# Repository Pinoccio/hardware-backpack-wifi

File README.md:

wifi-hardware-reference
===========================

Contained are the schematics, board layout, data sheets, and BOM for the Pinoccio WiFi board.

The board revisions are also marked as tags in the git repository, if you'd like to see a previous version.

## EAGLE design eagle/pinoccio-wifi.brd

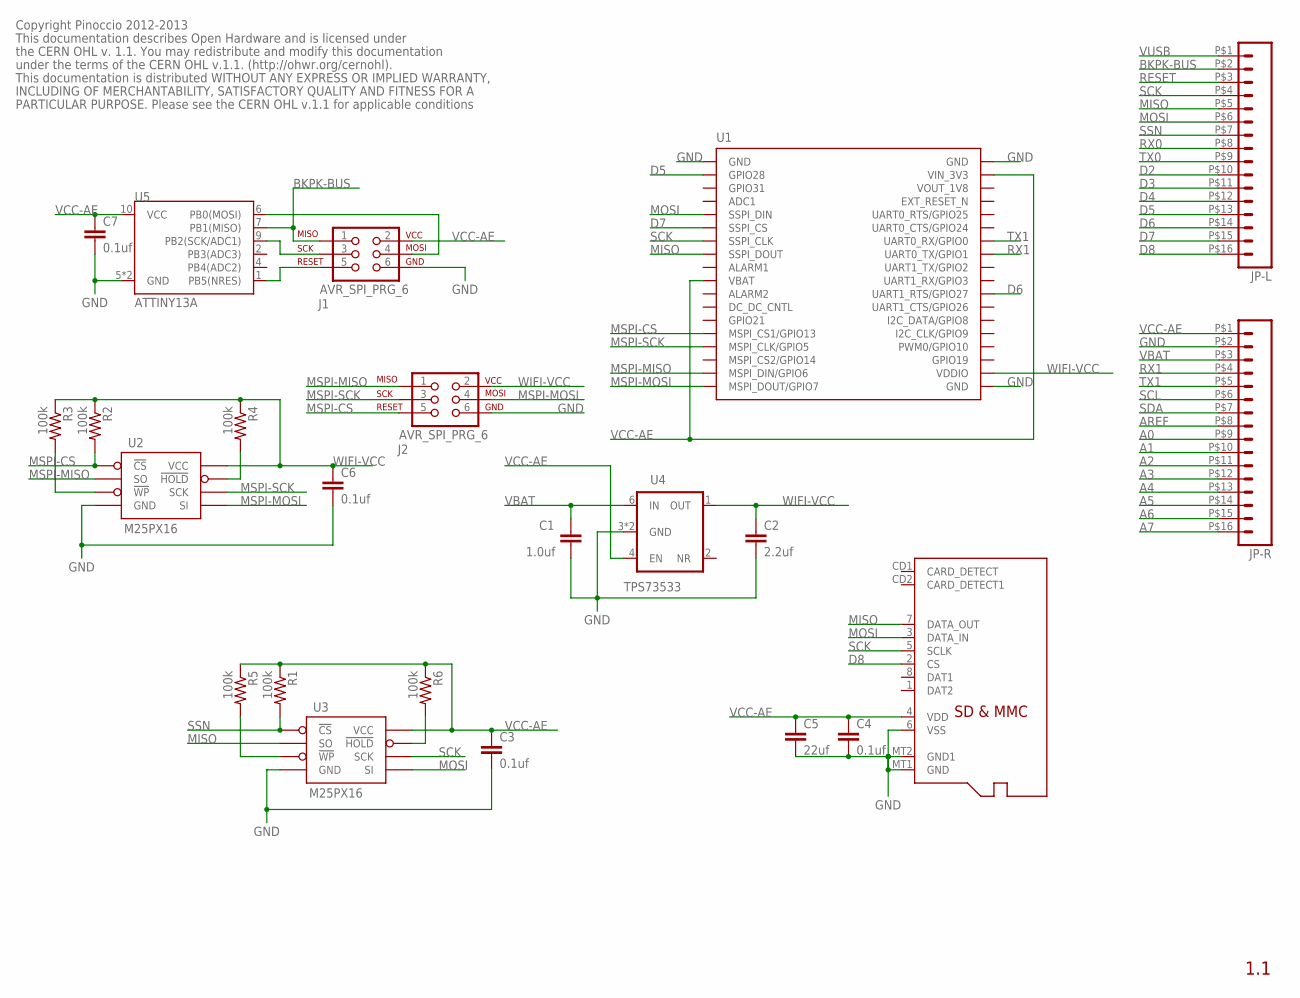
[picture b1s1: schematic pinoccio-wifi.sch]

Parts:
C1: 1.0uf; 0402-CAP
C2: 2.2uf; 0402-CAP
C3, C4, C6, C7: 0.1uf; 0402-CAP
C5: 22uf; 0603-CAP
J1, J2: AVR_SPI_PRG_6; 2X3-PAD
JP-L: M162MM; 1X16_2MM
JP-R: M162MM; 1X16_2MM
R1, R2, R3, R4, R5, R6: 100k; 0402-RES
U1: GS1011MIPS
U2, U3: M25PX16; SO8N
U4: TPS73533; SON-6-DRV
U5: ATTINY13A; QFN-10
U$1: MICROSD

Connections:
A0: JP-R.P$9 (9)
A1: JP-R.P$10 (10)
A2: JP-R.P$11 (11)
A3: JP-R.P$12 (12)
A4: JP-R.P$13 (13)
A5: JP-R.P$14 (14)
A6: JP-R.P$15 (15)
A7: JP-R.P$16 (16)
AREF: JP-R.P$8 (8)
BKPK-BUS: J1.1, JP-L.P$2 (2), U5.7 (PB1(MISO))
D2: JP-L.P$10 (10)
D3: JP-L.P$11 (11)
D4: JP-L.P$12 (12)
D5: JP-L.P$13 (13), U1.P$2 (GPIO28)
D6: JP-L.P$14 (14), U1.P$26 (UART1_RTS/GPIO27)
D7: JP-L.P$15 (15), U1.P$6 (SSPI_CS)
D8: JP-L.P$16 (16), U$1.2 (CS)
GND: C1.2, C2.2, C3.2, C4.2, C5.2, C6.2, C7.2, J1.6, J2.6, JP-R.P$2 (2), U1.P$1 (GND), U1.P$19 (GND), U1.P$36 (GND), U2.4 (GND), U3.4 (GND), U4.3 (GND), U4.PAD (GND), U5.5 (GND), U5.EP (GND), U$1.6 (VSS), U$1.MT1 (GND), U$1.MT2 (GND1)
MISO: JP-L.P$5 (5), U1.P$8 (SSPI_DOUT), U3.2 (SO), U$1.7 (DATA_OUT)
MOSI: JP-L.P$6 (6), U1.P$5 (SSPI_DIN), U3.5 (SI), U$1.3 (DATA_IN)
MSPI-CS: J2.5, R2.2, U1.P$14 (MSPI_CS1/GPIO13), U2.1 (!CS)
MSPI-MISO: J2.1, U1.P$17 (MSPI_DIN/GPIO6), U2.2 (SO)
MSPI-MOSI: J2.4, U1.P$18 (MSPI_DOUT/GPIO7), U2.5 (SI)
MSPI-SCK: J2.3, U1.P$15 (MSPI_CLK/GPIO5), U2.6 (SCK)
unnamed: R3.2, U2.3 (!WP)
unnamed: J1.4, U5.6 (PB0(MOSI))
unnamed: J1.3, U5.9 (PB2(SCK/ADC1))
unnamed: J1.5, U5.1 (PB5(NRES))
unnamed: R4.2, U2.7 (!HOLD)
unnamed: R6.2, U3.7 (!HOLD)
unnamed: R5.2, U3.3 (!WP)
RESET: JP-L.P$3 (3)
RX0: JP-L.P$8 (8)
RX1: JP-R.P$4 (4), U1.P$29 (UART0_TX/GPIO1)
SCK: JP-L.P$4 (4), U1.P$7 (SSPI_CLK), U3.6 (SCK), U$1.5 (SCLK)
SCL: JP-R.P$6 (6)
SDA: JP-R.P$7 (7)
SSN: JP-L.P$7 (7), R1.2, U3.1 (!CS)
TX0: JP-L.P$9 (9)
TX1: JP-R.P$5 (5), U1.P$30 (UART0_RX/GPIO0)
VBAT: C1.1, JP-R.P$3 (3), U4.6 (IN)
VCC-AE: C3.1, C4.1, C5.1, C7.1, J1.2, JP-R.P$1 (1), R1.1, R5.1, R6.1, U1.P$10 (VBAT), U1.P$35 (VIN_3V3), U3.8 (VCC), U4.4 (EN), U5.10 (VCC), U$1.4 (VDD)
VUSB: JP-L.P$1 (1)
WIFI-VCC: C2.1, C6.1, J2.2, R2.1, R3.1, R4.1, U1.P$20 (VDDIO), U2.8 (VCC), U4.1 (OUT)

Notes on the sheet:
1.1
Copyright Pinoccio 2012-2013
This documentation describes Open Hardware and is licensed under
the CERN OHL v. 1.1. You may redistribute and modify this documentation
under the terms of the CERN OHL v.1.1. (http://ohwr.org/cernohl).
This documentation is distributed WITHOUT ANY EXPRESS OR IMPLIED WARRANTY,
INCLUDING OF MERCHANTABILITY, SATISFACTORY QUALITY AND FITNESS FOR A
PARTICULAR PURPOSE. Please see the CERN OHL v.1.1 for applicable conditions

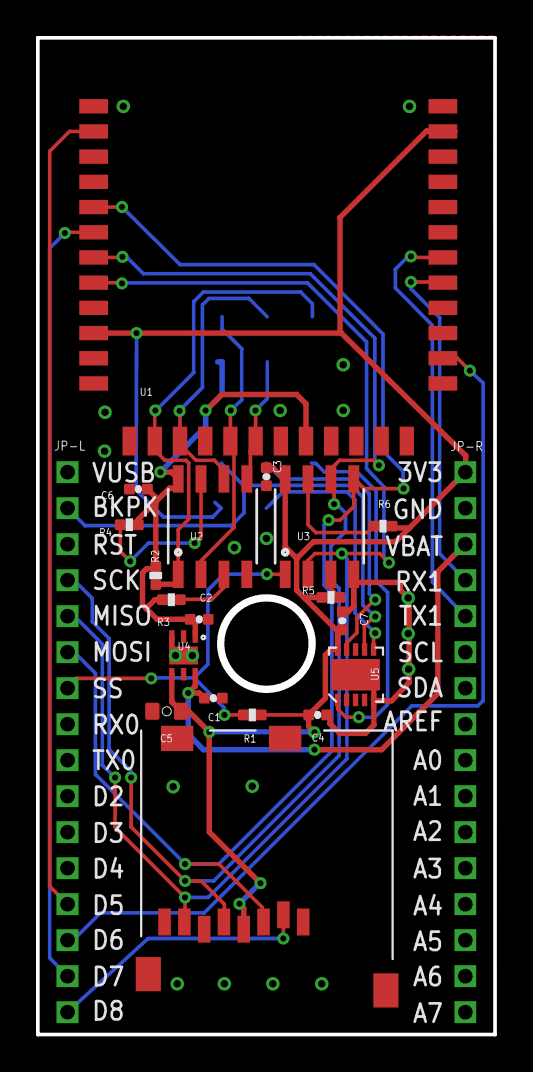
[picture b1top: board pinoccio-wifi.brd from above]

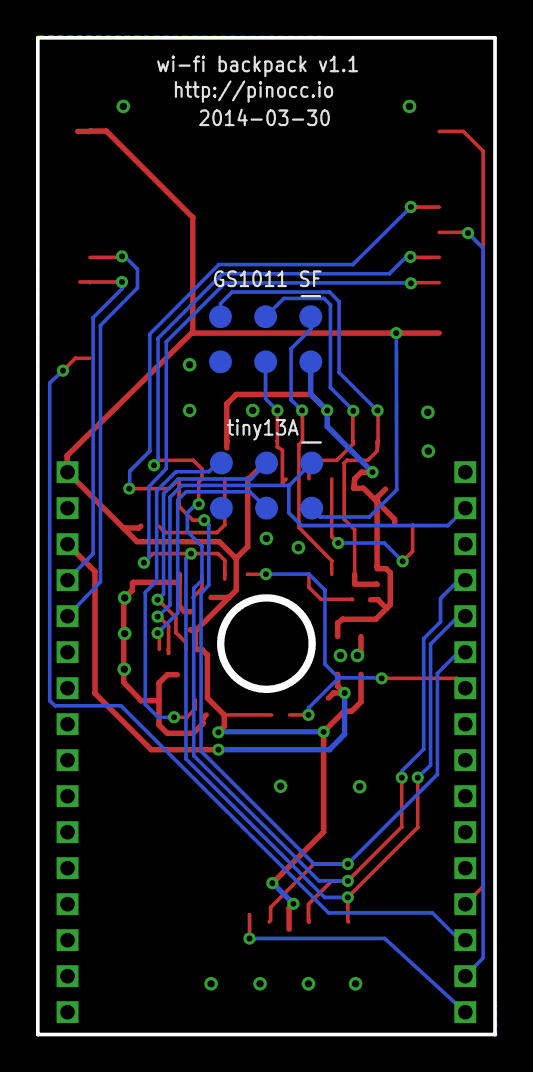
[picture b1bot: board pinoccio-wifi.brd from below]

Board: 2 copper layers, 25.2 x 55.2 mm, 23 parts (2 on the bottom side), 26 nets.

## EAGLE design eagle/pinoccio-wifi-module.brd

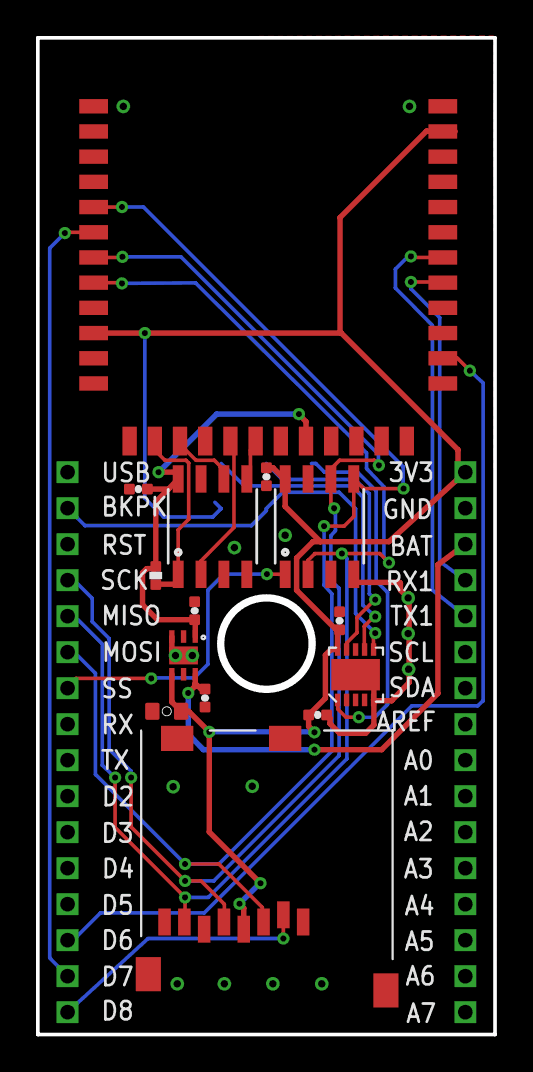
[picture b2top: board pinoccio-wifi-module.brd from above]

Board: 2 copper layers, 25.2 x 55.2 mm, 17 parts (1 on the bottom side), 21 nets.

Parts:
C1: 1.0uf; 0402-CAP
C2: 2.2uf; 0402-CAP
C3, C4, C6, C7: 0.1uf; 0402-CAP
C5: 22uf; 0603-CAP
GS1011MIPS: GS1011MIPS
J1: AVR_SPI_PRG_6; 2X3-PAD
JP-L: M162MM; 1X16_2MM
JP-R: M162MM; 1X16_2MM
R2: 10k; 0402-RES
U2: LDO-TPS73533; SON-6-DRV
U$1: MICROSD
U$2, U$4: M25PX16SO8N; SO8N
U$3: ATTINY13QFN10; QFN-10

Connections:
BKPK-BUS: J1.4, JP-L.P$2, U$3.6
D6: GS1011MIPS.P$26, JP-L.P$14
D7: GS1011MIPS.P$6, JP-L.P$15
D8: JP-L.P$16, U$1.2
GND: C1.2, C2.2, C3.2, C4.2, C5.2, C6.2, C7.2, GS1011MIPS.P$1, GS1011MIPS.P$19, GS1011MIPS.P$36, J1.6, JP-R.P$2, U2.3, U2.PAD, U$1.6, U$1.MT1, U$1.MT2, U$2.4, U$3.5, U$3.EP, U$4.4
MISO: GS1011MIPS.P$8, JP-L.P$5, U$1.7, U$2.2
MOSI: GS1011MIPS.P$5, JP-L.P$6, U$1.3, U$2.5
MSPI-CS: GS1011MIPS.P$14, R2.2, U$4.1
MSPI-MISO: GS1011MIPS.P$17, U$4.2
MSPI-MOSI: GS1011MIPS.P$18, U$4.5
MSPI-SCK: GS1011MIPS.P$15, U$4.6
unnamed: J1.1, U$3.7
unnamed: J1.3, U$3.9
unnamed: J1.5, U$3.1
RX1: GS1011MIPS.P$29, JP-R.P$4
SCK: GS1011MIPS.P$7, JP-L.P$4, U$1.5, U$2.6
SSN: JP-L.P$7, U$2.1
TX1: GS1011MIPS.P$30, JP-R.P$5
VBAT: C1.1, JP-R.P$3, U2.6
VCC-AE: C3.1, C4.1, C5.1, C7.1, GS1011MIPS.P$10, GS1011MIPS.P$35, J1.2, JP-R.P$1, U2.4, U$1.4, U$2.8, U$3.10
WIFI-VCC: C2.1, C6.1, GS1011MIPS.P$20, R2.1, U2.1, U$4.8

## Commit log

2012-12-15 Initial import
2012-12-15 update changes
2012-12-17 More fixups to capacitor design error and lack of enable
2012-12-17 Rename datasheet dir
2012-12-29 Revision v0.9
2013-01-01 Moar fixups
2013-01-03 Update datasheet and dioide layout to 0603
2013-07-08 v0.11 changes
2013-07-24 v0.11 datasheets
2013-07-24 removed incorrect boards
2013-07-24 Updated board to v0.13
2013-12-11 Fix #1: typo for VUSB
2013-12-11 Add S2W guides
2013-12-11 updated names of components for assembly
2013-12-11 Add gainspan AN054 note about SSL
2013-12-11 add PDFs of schems/board
2014-01-23 Add YAML file with EEPROM contents
    It is not final yet, but this is a better place than the
    pinoccio-backpack-reference repository where it was before.
2014-01-23 Update backpack EEPROM values
2014-02-17 Add Makefile for generating EEPROM contents
    This generates both a (semi) human-readable text version as well as the
    actual binary version.
2014-02-17 Add backpack bus firmware
    This copies the C code and Makefile from:
    https://github.com/Pinoccio/pinoccio-backpack-reference/tree/77ccd4f11e0b1e90f801a557d1fa426c624b5257/firmware
2014-03-11 Add v1.0 to changelog
2014-03-11 Add compiled backpack EEPROM contents and firmware
    The firmware was compiled using avr-gcc 4.7.3, on MacOS X.
2014-03-11 Version 1.1 PCB update
    - Connect D5 to Gainspan module GPIO28, for data-ready signal on SPI bus
    - Connect ATTiny13A PB3 to Gainspan module reset pin, with 10k pull-up
2014-03-30 Add v1.1 changes
2014-03-30 Add data-ready trace to D5
2014-04-01 Removed labels, updated build date
2014-04-01 Clean up PDFs
2014-06-27 Remove v1.0 pdfs again
    These pdfs are accessible through the v1.0 tag in git, no need to keep
    them in master.
2014-06-27 Update eeprom.yaml for v1.1
    This bumps the version number and adds the "rdy" pin, which connects to
    the SPI data ready pin on the GS1011.
2014-06-27 Show component names and values on the PCB
2014-06-27 Add compiled backpack EEPROM contents and firmware
    The firmware is the same compiled version as v1.0.
2014-07-03 Add bom

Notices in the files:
eagle/pinoccio-wifi-module.brd:
Licensed under CERN OHL v.1.1
